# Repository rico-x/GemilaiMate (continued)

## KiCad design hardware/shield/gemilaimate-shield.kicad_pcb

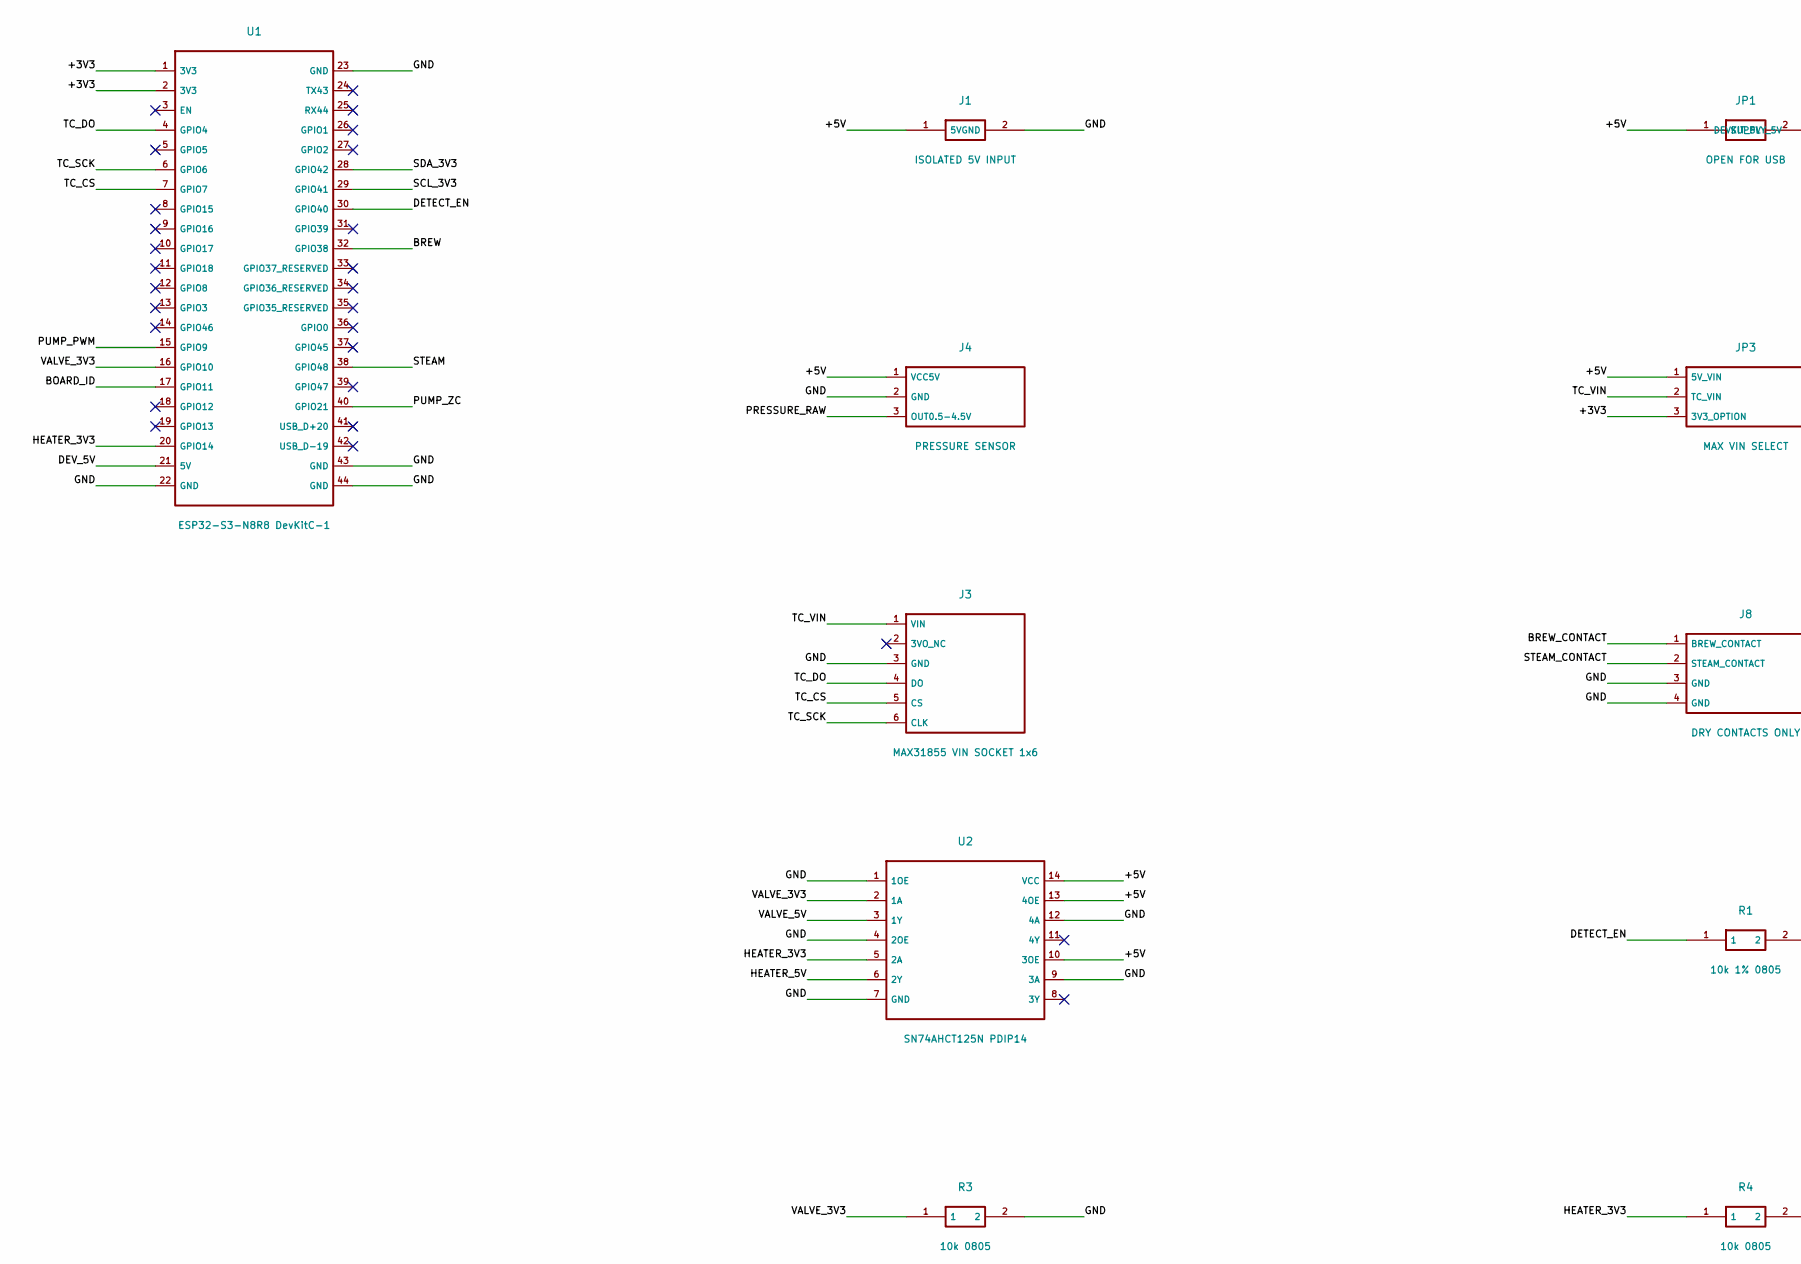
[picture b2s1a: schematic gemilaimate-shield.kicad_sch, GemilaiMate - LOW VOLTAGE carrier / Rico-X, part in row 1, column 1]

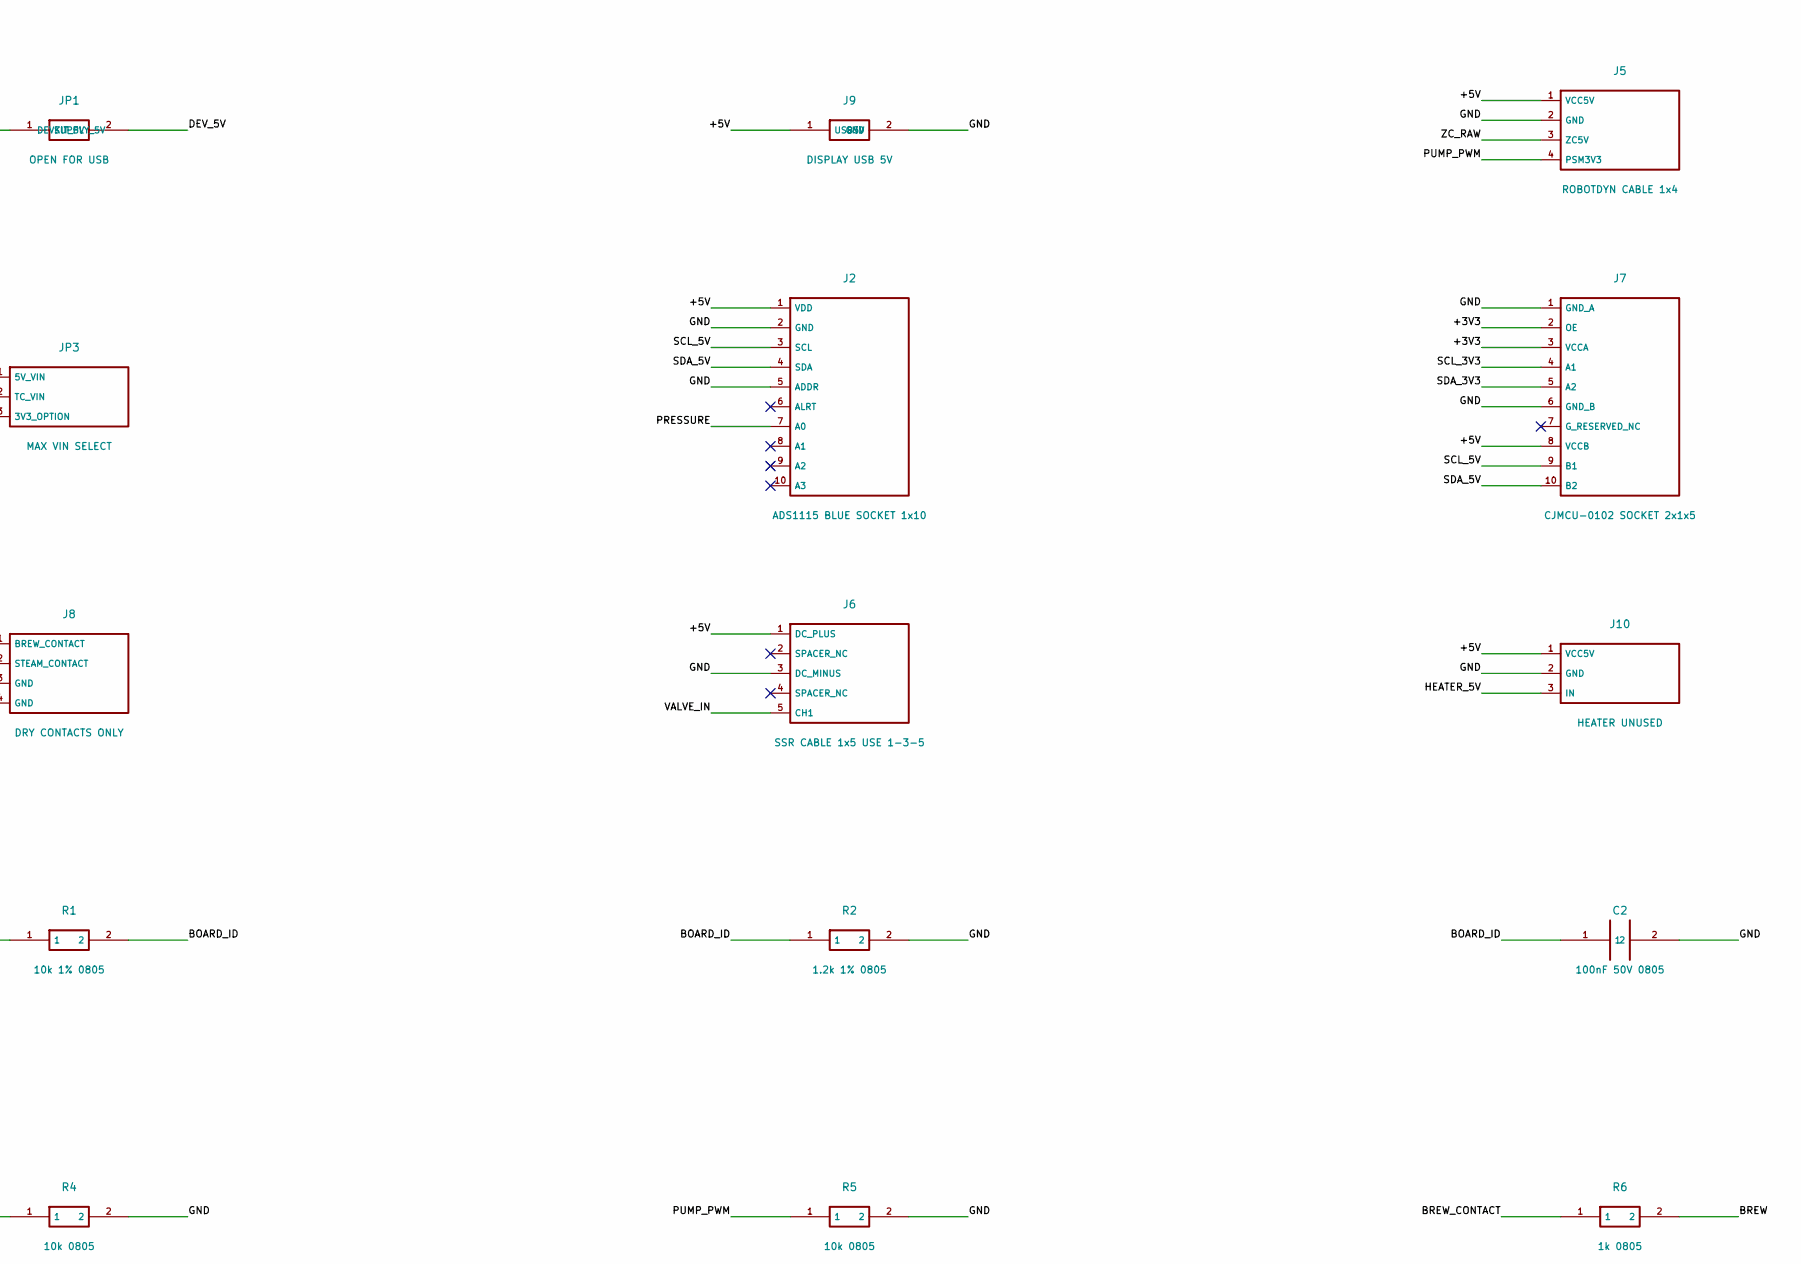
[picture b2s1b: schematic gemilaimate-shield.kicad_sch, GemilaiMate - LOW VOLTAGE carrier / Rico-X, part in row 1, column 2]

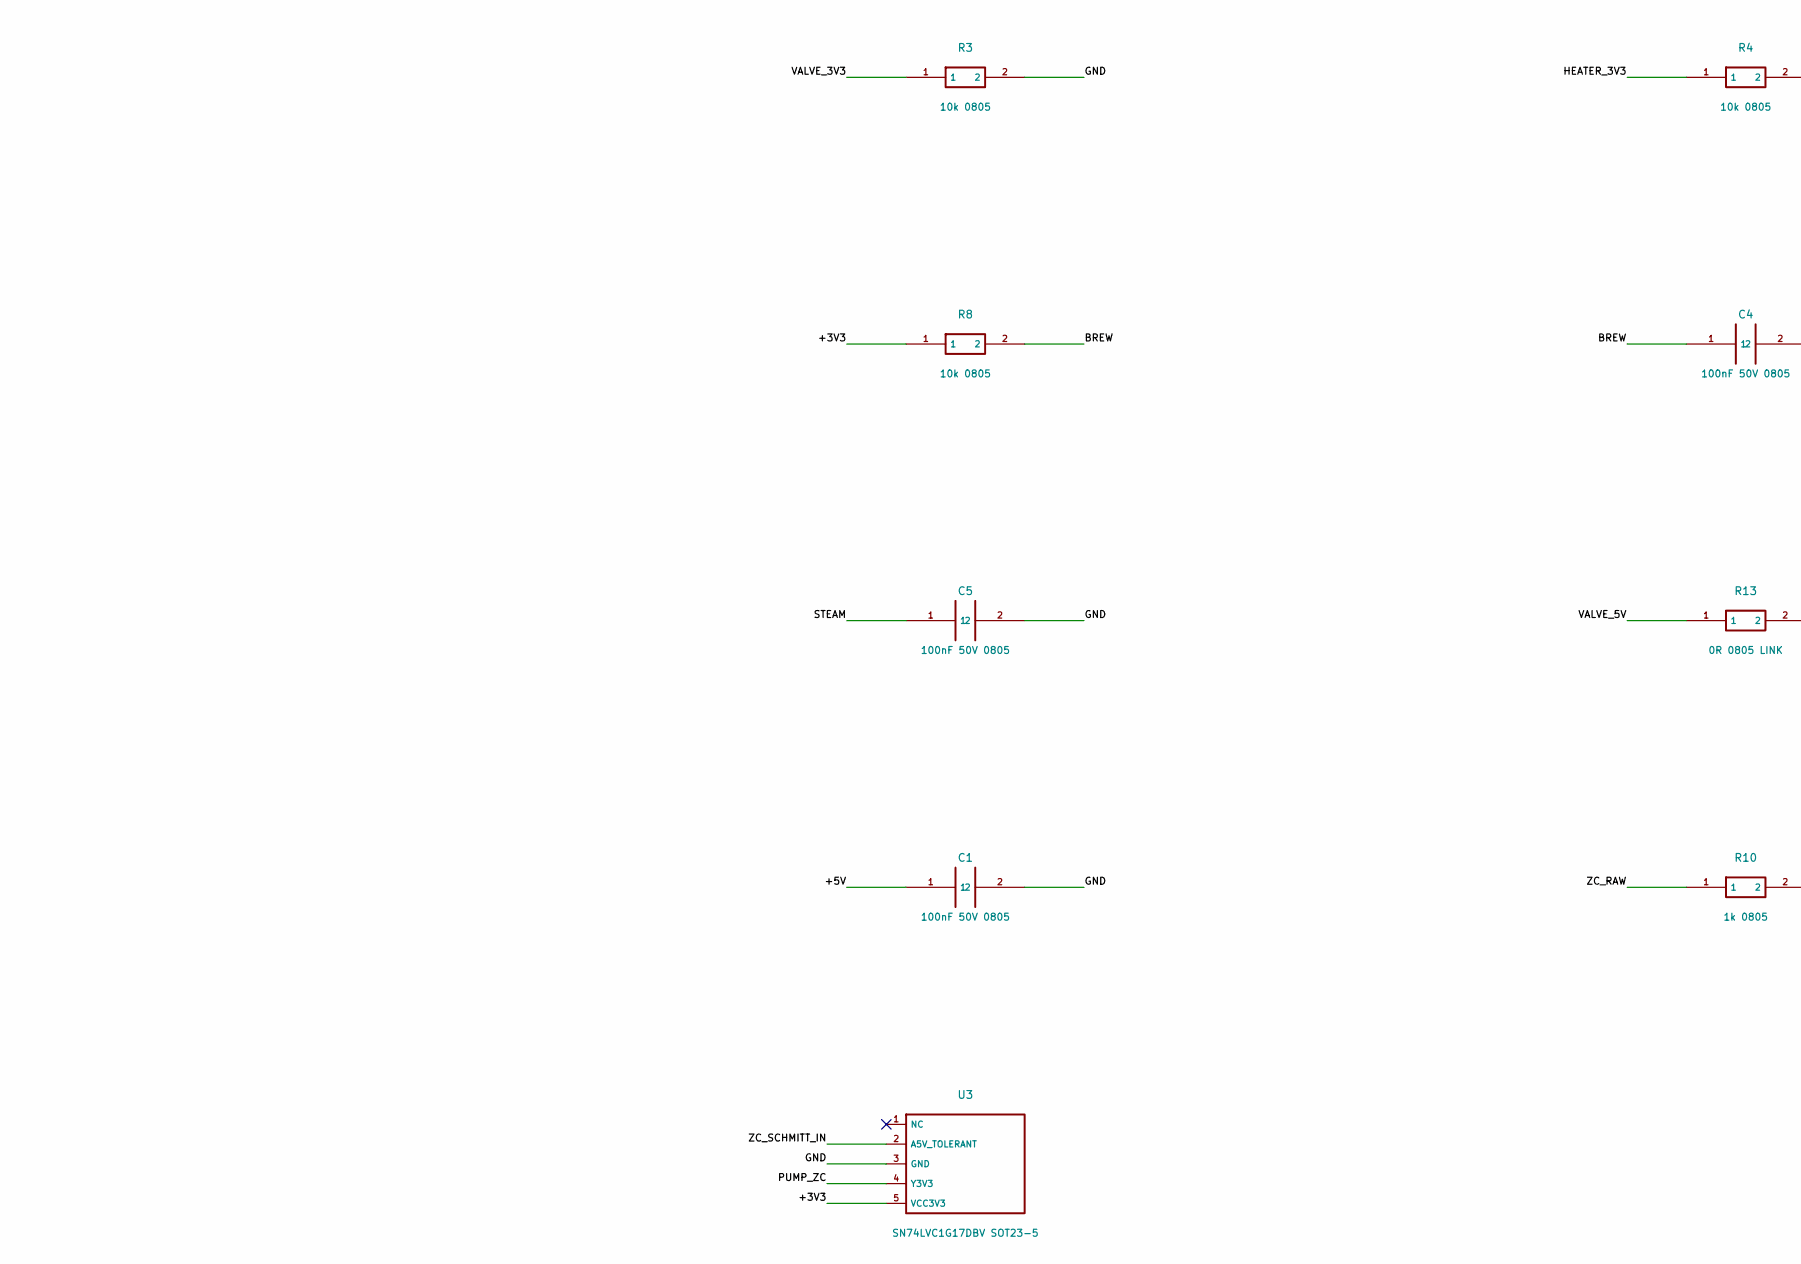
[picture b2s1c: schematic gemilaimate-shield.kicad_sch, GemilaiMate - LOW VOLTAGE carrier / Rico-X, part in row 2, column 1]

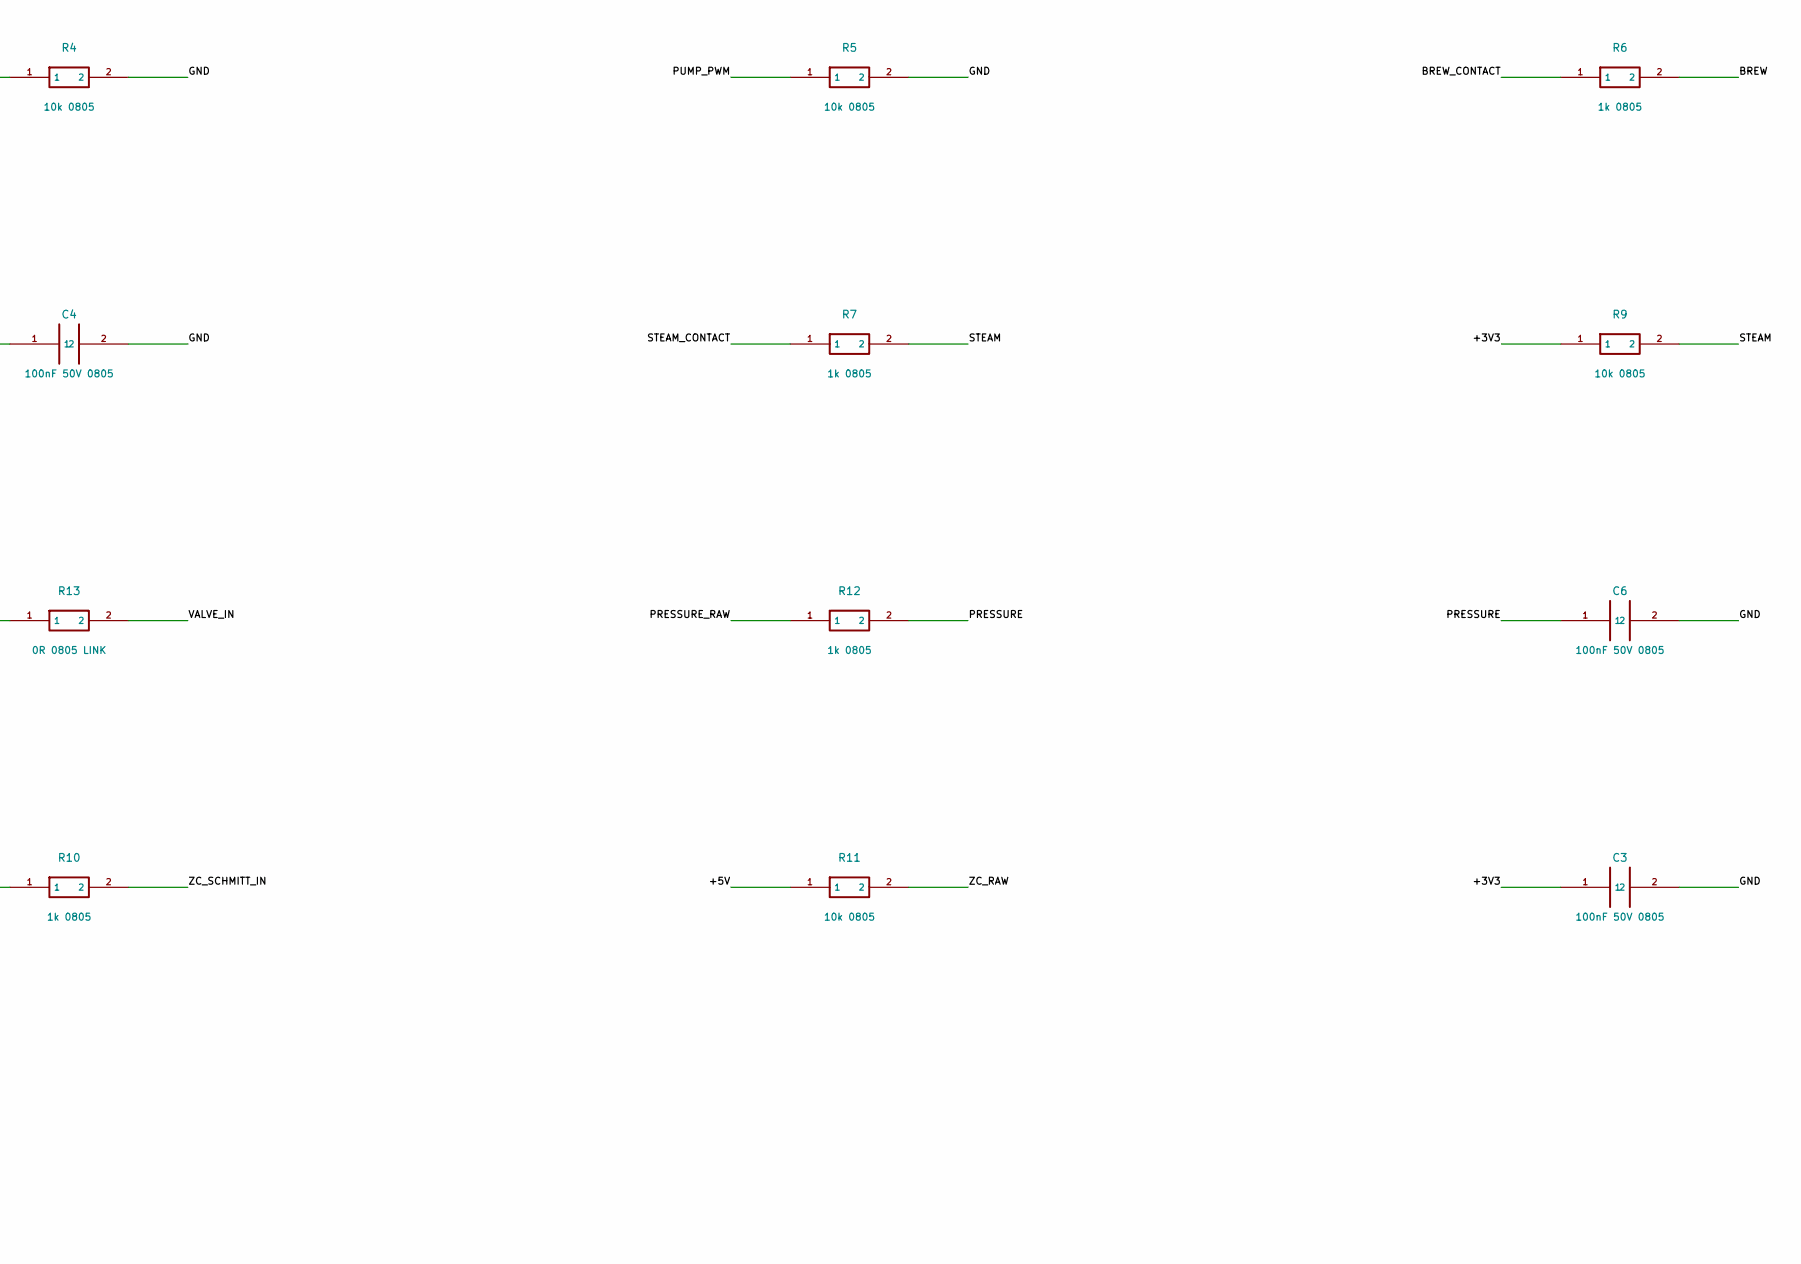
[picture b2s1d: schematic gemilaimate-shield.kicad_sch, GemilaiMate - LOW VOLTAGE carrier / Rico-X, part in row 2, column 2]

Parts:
C1: 100nF 50V 0805; C1_C_0805_2012Metric
C2: 100nF 50V 0805; C2_C_0805_2012Metric
C3: 100nF 50V 0805; C3_C_0805_2012Metric
C4: 100nF 50V 0805; C4_C_0805_2012Metric
C5: 100nF 50V 0805; C5_C_0805_2012Metric
C6: 100nF 50V 0805; C6_C_0805_2012Metric
J1: ISOLATED 5V INPUT; J1_header
J2: ADS1115 BLUE SOCKET 1x10; J2_socket_shield
J3: MAX31855 VIN SOCKET 1x6; J3_socket_shield
J4: PRESSURE SENSOR; J4_header
J5: ROBOTDYN CABLE 1x4; J5_socket_shield
J6: SSR CABLE 1x5 USE 1-3-5; J6_socket_shield
J7: CJMCU-0102 SOCKET 2x1x5; J7_socket_shield
J8: DRY CONTACTS ONLY; J8_header
J9: DISPLAY USB 5V; J9_header
J10: HEATER UNUSED; J10_header
JP1: OPEN FOR USB; JP1_header
JP3: MAX VIN SELECT; JP3_header
R1: 10k 1% 0805; R1_R_0805_2012Metric
R2: 1.2k 1% 0805; R2_R_0805_2012Metric
R3: 10k 0805; R3_R_0805_2012Metric
R4: 10k 0805; R4_R_0805_2012Metric
R5: 10k 0805; R5_R_0805_2012Metric
R6: 1k 0805; R6_R_0805_2012Metric
R7: 1k 0805; R7_R_0805_2012Metric
R8: 10k 0805; R8_R_0805_2012Metric
R9: 10k 0805; R9_R_0805_2012Metric
R10: 1k 0805; R10_R_0805_2012Metric
R11: 10k 0805; R11_R_0805_2012Metric
R12: 1k 0805; R12_R_0805_2012Metric
R13: 0R 0805 LINK; R13_R_0805_2012Metric
U1: ESP32-S3-N8R8 DevKitC-1; U1_ESP32
U2: SN74AHCT125N PDIP14; U2_DIP14
U3: SN74LVC1G17DBV SOT23-5; U3_SOT-23-5

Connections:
/+3V3: C3.1, J7.2 (OE), J7.3 (VCCA), JP3.3 (3V3_OPTION), R8.1, R9.1, U1.1 (3V3), U1.2 (3V3), U3.5 (VCC3V3)
/+5V: C1.1, J1.1 (5V), J2.1 (VDD), J4.1 (VCC5V), J5.1 (VCC5V), J6.1 (DC_PLUS), J7.8 (VCCB), J9.1 (USB5V), J10.1 (VCC5V), JP1.1 (SUPPLY_5V), JP3.1 (5V_VIN), R11.1, U2.10 (3OE), U2.13 (4OE), U2.14 (VCC)
/BOARD_ID: C2.1, R1.2, R2.1, U1.17 (GPIO11)
/BREW: C4.1, R6.2, R8.2, U1.32 (GPIO38)
/BREW_CONTACT: J8.1 (BREW_CONTACT), R6.1
/DETECT_EN: R1.1, U1.30 (GPIO40)
/DEV_5V: JP1.2 (DEVKIT_5V), U1.21 (5V)
/GND: C1.2, C2.2, C3.2, C4.2, C5.2, C6.2, J1.2 (GND), J2.2 (GND), J2.5 (ADDR), J3.3 (GND), J4.2 (GND), J5.2 (GND), J6.3 (DC_MINUS), J7.1 (GND_A), J7.6 (GND_B), J8.3 (GND), J8.4 (GND), J9.2 (GND), J10.2 (GND), R2.2, R3.2, R4.2, R5.2, U1.22 (GND), U1.23 (GND), U1.43 (GND), U1.44 (GND), U2.1 (1OE), U2.4 (2OE), U2.7 (GND), U2.9 (3A), U2.12 (4A), U3.3 (GND)
/HEATER_3V3: R4.1, U1.20 (GPIO14), U2.5 (2A)
/HEATER_5V: J10.3 (IN), U2.6 (2Y)
/PRESSURE: C6.1, J2.7 (A0), R12.2
/PRESSURE_RAW: J4.3 (OUT0.5-4.5V), R12.1
/PUMP_PWM: J5.4 (PSM3V3), R5.1, U1.15 (GPIO9)
/PUMP_ZC: U1.40 (GPIO21), U3.4 (Y3V3)
/SCL_3V3: J7.4 (A1), U1.29 (GPIO41)
/SCL_5V: J2.3 (SCL), J7.9 (B1)
/SDA_3V3: J7.5 (A2), U1.28 (GPIO42)
/SDA_5V: J2.4 (SDA), J7.10 (B2)
/STEAM: C5.1, R7.2, R9.2, U1.38 (GPIO48)
/STEAM_CONTACT: J8.2 (STEAM_CONTACT), R7.1
/TC_CS: J3.5 (CS), U1.7 (GPIO7)
/TC_DO: J3.4 (DO), U1.4 (GPIO4)
/TC_SCK: J3.6 (CLK), U1.6 (GPIO6)
/TC_VIN: J3.1 (VIN), JP3.2 (TC_VIN)
/VALVE_3V3: R3.1, U1.16 (GPIO10), U2.2 (1A)
/VALVE_5V: R13.1, U2.3 (1Y)
/VALVE_IN: J6.5 (CH1), R13.2
/ZC_RAW: J5.3 (ZC5V), R10.1, R11.2
/ZC_SCHMITT_IN: R10.2, U3.2 (A5V_TOLERANT)

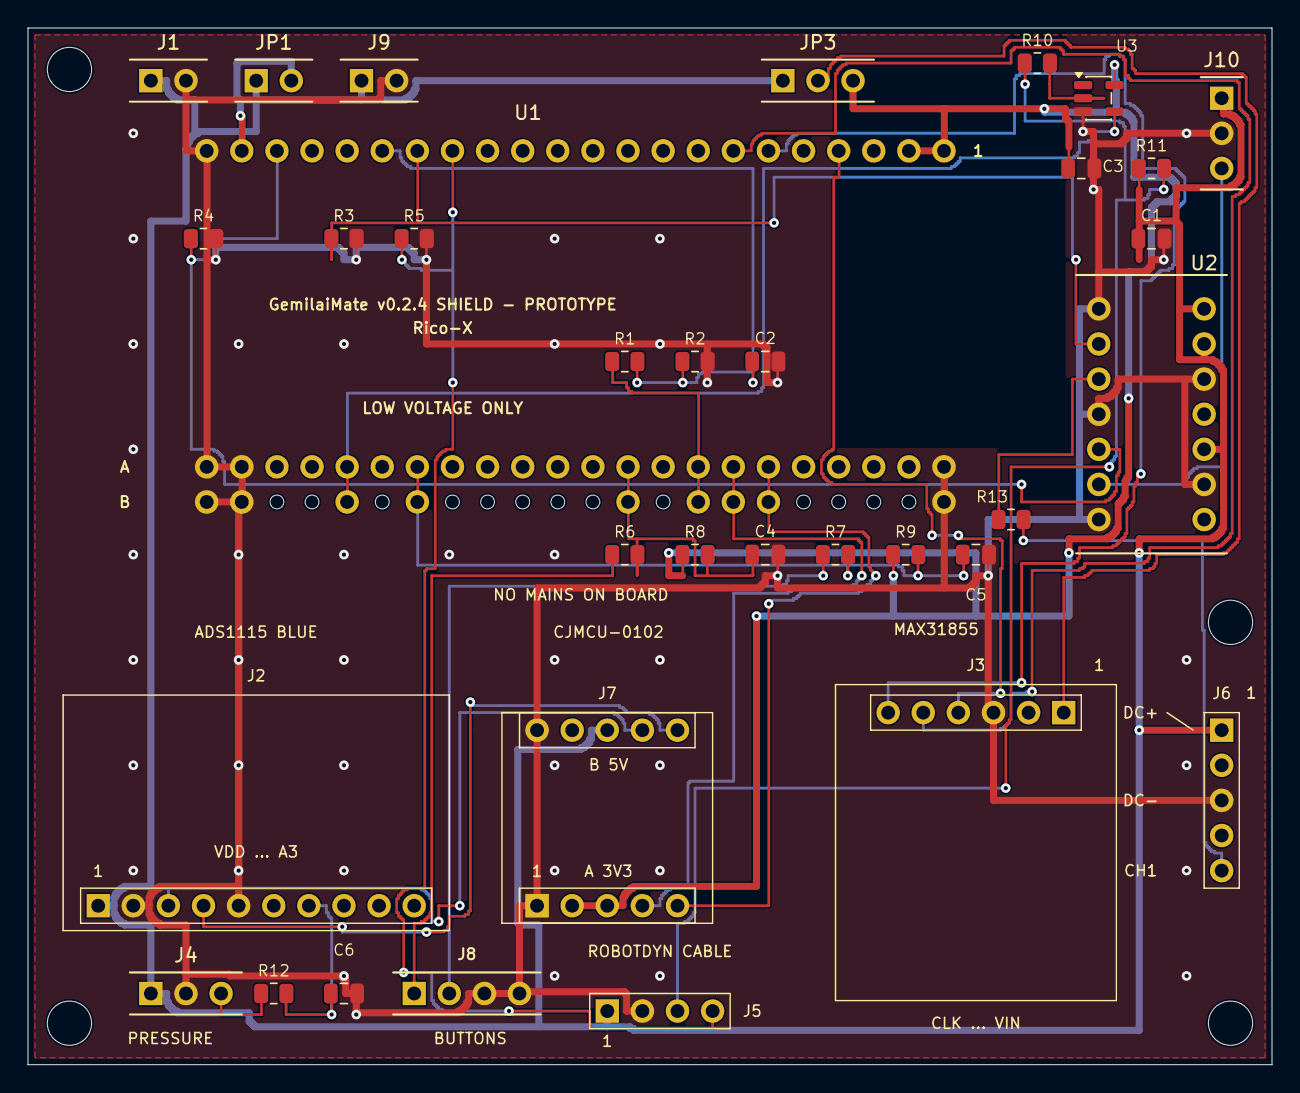
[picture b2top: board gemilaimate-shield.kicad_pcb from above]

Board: 2 copper layers, 90.0 x 75.0 mm, 36 parts (0 on the bottom side), 29 nets.

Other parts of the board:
H1, H2: M3

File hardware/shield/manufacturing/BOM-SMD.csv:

Designators,Quantity_per_board,Requirement,Package,Manufacturer_example,MPN_example
R1 R3 R4 R5 R8 R9 R11,7,10k 1% >=0.125W,0805,Yageo,RC0805FR-0710KL
R2,1,1.2k 1% >=0.125W,0805,Yageo,RC0805FR-071K2L
R6 R7 R10 R12,4,1k 1% >=0.125W,0805,Yageo,RC0805FR-071KL
R13,1,0 ohm jumper,0805,Yageo,RC0805JR-070RL
C1 C2 C3 C4 C5 C6,6,100nF 50V X7R +/-10%,0805,Samsung,CL21B104KBCNNNC
U3,1,Non-inverting Schmitt; 5.5V input; 3.3V VCC,SOT-23-5 DBV,Texas Instruments,SN74LVC1G17DBVR

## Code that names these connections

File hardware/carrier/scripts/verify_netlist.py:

import json,re
from pathlib import Path
import sexpdata
import os
out=Path(__file__).resolve().parents[1]
source_root=Path(os.environ.get('GEMILAIMATE_FIRMWARE', str(out.parents[1]/'firmware')))
spec=json.loads((out/'design.json').read_text())
t=sexpdata.loads((out/'gemilaimate-carrier.net').read_text())
get=lambda x,k:next((a[1:] for a in x if isinstance(a,list) and str(a[0])==k),[])
netnodes={}; mapping={}
for n in get(t,'nets'):
 name=get(n,'name')[0];nodes=[]
 for a in n:
  if isinstance(a,list) and str(a[0])=='node':
   ref=get(a,'ref')[0];pin=str(get(a,'pin')[0]);nodes.append((ref,pin));mapping[ref+'.'+pin]=name
 netnodes[name]=set(nodes)
expected={}
for c in spec['parts']:
 for pin in c['pins']:
  if pin['net']:expected.setdefault('/'+pin['net'],set()).add((c['ref'],pin['number']))
assert {k:v for k,v in netnodes.items() if not k.startswith('unconnected-')}==expected
assert all(len(v)==1 for k,v in netnodes.items() if k.startswith('unconnected-'))
(out/'schematic-pad-nets.json').write_text(json.dumps(mapping,indent=2))

# Independent comparison against the pinned firmware configuration, rather
# than merely comparing two files generated from the same placement data.
source=(source_root/'lib/GemilaiMateController/src/ControllerConfig.h').read_text()
block=source.split('const ControllerConfig GEMILAI_3007Z =',1)[1].split('const ControllerConfig',1)[0]
actual={k:int(v) for k,v in re.findall(r'\.(\w+)\s*=\s*(\d+)',block)}
functions={'pumpPin':'PUMP_PWM','pumpSensePin':'PUMP_ZC','valvePin':'VALVE_3V3','heaterPin':'HEATER_3V3','pressureScl':'SCL_3V3','pressureSda':'SDA_3V3','maxSckPin':'TC_SCK','maxCsPin':'TC_CS','maxMisoPin':'TC_DO','brewButtonPin':'BREW','steamButtonPin':'STEAM'}
mcu=next(x for x in spec['parts'] if x['ref']=='U1')
verified={}
for field,nn in functions.items():
 pin=next(x for x in mcu['pins'] if x['net']==nn)
 number=int(pin['name'].replace('GPIO',''))
 assert number==actual[field],(field,number,actual[field])
 verified[field]={'gpio':number,'carrier_pin':'U1.'+pin['number'],'net':nn}
assert all(x['net'] is None for x in mcu['pins'] if x['name'].endswith('_RESERVED'))
header=(source_root/'lib/GemilaiMateController/src/GemilaiMateController.h').read_text()
for field,nn in [('DETECT_EN_PIN','DETECT_EN'),('DETECT_VALUE_PIN','BOARD_ID')]:
 pin=next(x for x in mcu['pins'] if x['net']==nn)
 number=int(pin['name'].replace('GPIO',''))
 assert number==int(re.search(r'constexpr int '+field+r'\s*=\s*(\d+)',header).group(1))
 verified[field]={'gpio':number,'carrier_pin':'U1.'+pin['number'],'net':nn}

# DC and settling analysis: the 30-60k pull values are stress scenarios, not datasheet limits.
import math,itertools
rt,rb=10000,1200
unloaded=[];loaded=[];settled=[]
for supply,top,bottom,cap,pull in itertools.product([3.3*.95,3.3*1.05],[rt*.99,rt*1.01],[rb*.99,rb*1.01],[100e-9*.8,100e-9*1.2],[30000,45000,60000]):
 inf=supply*bottom/(top+bottom);eff=1/(1/bottom+1/pull)
 unloaded.append(inf*1000);loaded.append(supply*eff/(top+eff)*1000)
 tau=1/(1/top+1/bottom)*cap
 settled.append(inf*(1-math.exp(-.010/tau))*1000)
report_values={'top_ohm':rt,'bottom_ohm':rb,'unloaded_mv':[min(unloaded),max(unloaded)],'pulldown_scenario_30k_to_60k_mv':[min(loaded),max(loaded)],'settled_10ms_from_zero_mv':[min(settled),max(settled)]}
assert all(300 < x < 400 for x in report_values['pulldown_scenario_30k_to_60k_mv'])
assert all(300 < x < 400 for x in report_values['settled_10ms_from_zero_mv'])
cpp=(source_root/'lib/GemilaiMateController/src/GemilaiMateController.cpp').read_text().split('void GemilaiMateController::detectBoard()',1)[1].split('void GemilaiMateController::detectAddon()',1)[0]
assert cpp.index('pinMode(DETECT_VALUE_PIN, ANALOG)')<cpp.index('adcAttachPin(DETECT_VALUE_PIN)')<cpp.index('delay(10)')
assert 'INPUT_PULLDOWN' not in cpp
byref={x['ref']:x for x in spec['parts']}
assert byref['R1']['value'].startswith('10k') and byref['R2']['value'].startswith('1.2k')
assert [x['net'] for x in byref['U3']['pins']]==[None,'ZC_SCHMITT_IN','GND','PUMP_ZC','+3V3']
assert not any(x['ref']=='J11' for x in spec['parts'])
assert spec['size_mm']==[90,46]
# Closed-contact LOW with 1k series and 10k || internal pull-up: safely below 0.25 VDD for the stated stress range.
button_ratio=max(1000*1.01/(1000*1.01+1/(1/(10000*.99)+1/pull)) for pull in [30000,45000,60000])
assert button_ratio<.25
report={'schematic_connectivity_matches_design':True,'connected_nets':len(expected),'source_version':spec['source_version'],'firmware_ref':spec['firmware_ref'],'firmware_pin_checks':verified,'gpio35_36_37_unused':True,'divider':report_values,'adc_attached_before_settling':True,'adc_settling_ms':10,'board_id_window_mv':[300,400],'button_closed_low_ratio_vdd_worst_scenario':button_ratio,'zc_interface':'SN74LVC1G17DBV at 3V3, 5.5V-tolerant input; no TXS on ZC','mechanical_reference_size_mm':[90,46],'mechanical_clone_and_mounts_not_verified':True,'electrical_limits':['30-60kohm internal pulls are scenario values, not guaranteed component limits.','ADC error, GPIO source impedance and physical variation still need bench measurement.','ERC does not model module internals or certify mains isolation.','No physical assembly or USB upload has been performed.']}
(out/'verification.json').write_text(json.dumps(report,indent=2))
print('Connectivity and 13 GPIO checks pass; current divider:',report_values)

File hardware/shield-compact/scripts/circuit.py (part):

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                dict(enumerate(labels, 1)), angle=angle, side='back', section='Connectors', dnp=dnp)


GPIO_NET = {0:'BOOT',1:'EXT1',2:'EXT2',3:'STRAP3',4:'TC_DO',5:'GPIO5',
  6:'TC_SCK',7:'TC_CS',8:'EXT3',9:'PUMP_PWM',10:'VALVE',11:'BOARD_ID',
  12:'EXT4',13:'EXT5',14:'HEATER',15:'GPIO15',16:'GPIO16',17:'SCALE_CLK',
  18:'SCALE_DAT0',19:'USB_DM_MCU',20:'USB_DP_MCU',21:'PUMP_ZC',
  38:'BREW',39:'SCALE_DAT1',40:'DETECT_EN',41:'SCL_3V3',42:'SDA_3V3',
  43:'ALBA_SDA',44:'ALBA_SCL',45:'STRAP45',46:'STRAP46',47:'ALT',48:'STEAM'}
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     {1:'+3V3',2:'GND',3:'EXT1',4:'EXT2',5:'EXT3',6:'EXT4',7:'EXT5',8:'+5V_EXT',9:'GND',10:'GND'},
     section='Expansion',dnp=True)
part('J_FREE','FREE GPIO 3V3','Connector_PinHeader_2.54mm:PinHeader_1x06_P2.54mm_Vertical',(32,12.5),
     {1:'+3V3',2:'GND',3:'GPIO5',4:'GPIO15',5:'GPIO16',6:'GND'},angle=90,section='Expansion',dnp=True)
# Keep the legacy cable connector designators stable; this inserted module socket
# is appended after the existing J1-J18 connectors. Row order follows the CJMCU
# silkscreen (A: GND OE VA A1 A2, B: GND G VB B1 B2) and TI SCES640L Table 4-1:
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            size_mm=json.loads((HERE/'layout-config.json').read_text())['size_mm'], copper_layers=2, author='Rico-X',
            repository='https://github.com/Rico-X/GemilaiMate',
            hardware_tested=False, manufacturing_release=False, mains_on_board=False,
            board_id=4, physical_flash_mb=16, compatible_partition_flash_mb=8,
            psram_mb=8, peripheral_gpio={'sda':43,'scl':44},
            rf_keepout=[5.5+json.loads((HERE/'layout-config.json').read_text()).get('layout_offset_x_mm',0),-8,24.5+json.loads((HERE/'layout-config.json').read_text()).get('layout_offset_x_mm',0),-.1],
            module_body=[6+json.loads((HERE/'layout-config.json').read_text()).get('layout_offset_x_mm',0),-7.15,24+json.loads((HERE/'layout-config.json').read_text()).get('layout_offset_x_mm',0),18.35],
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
